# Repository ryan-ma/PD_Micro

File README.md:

# PD_Micro
ATMega32U4 Arduino board with USB-C PD Power Delivery and PPS

## Specs:
- ATmega32U4 running at 5 V and 16 MHz
- FUSB302 USB-C PHY (USB PD communication on CC pins)
- TPS62175 DC-DC for 5-20V input, 5V 500mA max output
- On-board 30V 10.4A P-channel MOSFET load switch
- 5 LEDs for power delivery voltage level
- 3 LEDs for power delivery current level
- 3.5 mm, 2 position terminal block for power output
- 1.6 x 0.7 inches (0.3 inches longer than pro micro)

# Basic Usage

Open `PD_Micro.ino` with Arduino Sketch. Choose board `Arduino Leoardo`

## Set power option
Allocate a PD_UFP object
```
class PD_UFP_c PD_UFP;
```

Initialize it with one of the power options. That sets the maximum voltage/current. 
```
PD_UFP.init(PD_POWER_OPTION_MAX_20V);
```

```
enum PD_power_option_t {
    PD_POWER_OPTION_MAX_5V      = 0,
    PD_POWER_OPTION_MAX_9V      = 1,
    PD_POWER_OPTION_MAX_12V     = 2,
    PD_POWER_OPTION_MAX_15V     = 3,
    PD_POWER_OPTION_MAX_20V     = 4,
    PD_POWER_OPTION_MAX_VOLTAGE = 5,
    PD_POWER_OPTION_MAX_CURRENT = 6,
    PD_POWER_OPTION_MAX_POWER   = 7,
};
```

## Run USB PD state machine
Before USB PD negotiation had completed, `PD_UFP.run()` must be called in a short interval, less than 10ms, to ensure state machine response to negotiation message in time. Long response time may result in a power reset cycle initiated by USB PD hosts.

## Wait for USB PD negotiation completed
`PD_UFP.is_power_ready()` is set when
- PD negotiation completed, PD host sent a power ready message, or
- PD host not exist, CC pins voltage is checked and the power level determined.

The negotiation process typically takes less than a second.

## Examine the negotiated power value
Examine the negotiated power value. Turn on the load switch only when the power requirements are met. PD Micro itself does not have PD over current protection. Any excessive power usage may trigger USB PD host power protection, result in voltage dip and MCU reset. 

```
PD_UFP.run();
if (PD_UFP.get_voltage() == PD_V(20.0) && PD_UFP.get_current() >= PD_A(1.5)) {
  PD_UFP.set_output(1);   // Turn on load switch 
  PD_UFP.set_led(1);      // Output reach 20V and 1.5A, set indicators on
} else {
  PD_UFP.set_output(0);   // Turn off load switch
  PD_UFP.blink_led(400);  // Output less than 20V or 1.5A, blink LED
}
```
For Fix power option, `PD_UFP.get_voltage()` in 50 mV units and `PD_UFP.get_current()` in 10mA units. Use marco `PD_V` and `PD_A` to simplify conversion.

## Changing power option in run time
Power options can be changed any time after PD negotiation.
```
PD_UFP.set_power_option(PD_POWER_OPTION_MAX_20V);
```

`PD_UFP.is_ps_transition()` is set during power transition, clear when new power is ready. 
Power transition takes a maximum time of 550ms according to PD specifications. Depends on the power adapter, it is usually shorter.

# USB PD 3.0 PPS (Programmable Power Supply)
USB PD3.0 introduces a new PPS (Programmable Power Supply) mode. If PD source supports PPS, It allows devices to negotiate precise voltage range from 3.3V to 5.9/11/16/21 V with 20 mV step. PPS also supports a coarse current limit, with the value in 50 mA step.

The library provides another set of procedures to request PPS. If source PPS is not available or not qualified, it will fall back to use the regular PD power option.

## Set voltage and current on startup
Instead of using `PD_UFP.init()`, use `PD_UFP.init_PPS()` to setup PPS voltage in 20 mV units and PPS current in 50 mA units. Use marco `PPS_V()` and `PPS_A()` to simplify conversion.
```
PD_UFP.init_PPS(PPS_V(4.2), PPS_A(2.0));
```
The default fall-back PD power option is 5V. It can be changed by an extra parameter.
```
PD_UFP.init_PPS(PPS_V(4.2), PPS_A(2.0), PD_POWER_OPTION_MAX_9V);
```

PD Micro use ATMega32U4 with safe operation 8MHz @ <4.5V. To request PPS below 4.5V, use `clock_prescale_set(clock_div_2)` to slow down the working frequency, and use `PD_UFP.clock_prescale_set(2)` to prescale the library internal clock.
```
PD_UFP.clock_prescale_set(2);
clock_prescale_set(clock_div_2);
```

## Wait for USB PD PPS trigger completed
Once PD negotiation is completed,
- If PPS is available and qualified, `PD_UFP.is_PPS_ready()` is set. 
- If PPS is not available or qualified, `PD_UFP.is_power_ready()` is set.

If PPS is successfully triggered, the output voltage and current will be the exact value provided in the startup. It is not required to examine negotiated voltage and current.
```
PD_UFP.run();
if (PD_UFP.is_PPS_ready()) {          // PPS trigger success
  PD_UFP.set_output(1);               // Turn on load switch 
  PD_UFP.set_led(1);                  // PPS output 4.2V 2.0A ready
} else if (PD_UFP.is_power_ready()) { // Fail to trigger PPS, fall back
  PD_UFP.set_output(0);               // Turn off load switch
  PD_UFP.blink_led(400);              // blink LED
}
```
For PPS, `PD_UFP.get_voltage()` in 20 mV units and `PD_UFP.get_current()` in 50 mA units. Use marco `PPS_V()` and `PPS_A()` to simplify conversion.

## Changing PPS voltage and current in run time
PPS settings can be changed any time after PPS ready. Similar to `PD_UFP.init_PPS()`, set voltage in 20 mV units and current in 50 mA units. Use Marco `PPS_V()` and `PPS_A()` to simplify conversion.
```
PD_UFP.set_PPS(PPS_V(3.3), PPS_A(2.0));
```

`PD_UFP.is_ps_transition()` is set during power transition, clear when new power is ready. 
Power transition takes a maximum time of 550 ms according to specification. It is usually less than 50ms in PPS mode. 

By calling `PD_UFP.set_PPS()`, the library re-evaluates all PPS source capabilities to find the best fit. If it fails to find one, it returns false, no power request, and power transition will happen.

To exit PPS mode, call `PD_UFP.set_power_option()` to clear PPS setting and fall back to regular power option mode.

# LED Indicators
There are 5 LEDs for voltage and 3 LEDs for current on PD_Micro, multiplexed by 6 internal IO pins. These are managed by the PD_UFP library. 

The library turn on voltage LED according to the following table

| Voltage Range | LED | 
| --- | --- |
| >= 3.3V && < 9V | 5V | 
| >= 9V && < 12V | 9V | 
| >= 12V && < 15V | 12V | 
| >= 15V && < 20V | 15V | 
| >= 20 | 20V | 

# Debugging
The library can log library status, source capabilities, protocol packets, with timestamps in the millisecond step to the serial port.

To use it, allocate PD_UFP object with derived class `PD_UFP_log_c`
```
class PD_UFP_log_c PD_UFP;
```
initialize hardware serial1 in setup.
```
void setup() {
  Serial1.begin(115200);
  ...
```
call `PD_UFP.print_status(Serial1)` inside `loop()`.
```
void loop() {
  PD_UFP.run();
  PD_UFP.print_status(Serial1);
  ...
```
Connect Pin 1 (PD3 / UART TX) and GND to external USB to UART to read serial messages.

PD Micro can be converted to serial passthrough mode and use it as USB to UART. I included these Arduino sketch examples in <a href="/examples">examples</a> folder.

## Debug raw packets
The library provides two log levels. Initialize PD_UFP with extra parameter `PD_LOG_LEVEL_VERBOSE` to output raw packets
```
class PD_UFP_log_c PD_UFP(PD_LOG_LEVEL_VERBOSE);
```
```
enum pd_log_level_t {
    PD_LOG_LEVEL_INFO,
    PD_LOG_LEVEL_VERBOSE
};
```

# Bootloader
PD Micro uses `Caterina-promicro16.hex` bootloader provided by Sparkfun. Program it by `avrdude` and set the corresponding `efuse`.
```
avrdude -p m32u4 -P usb -c avrispmkii -U flash:w:Caterina-promicro16.hex -U efuse:w:0xcb:m -U hfuse:w:0xd8:m -U lfuse:w:0xff:m
```

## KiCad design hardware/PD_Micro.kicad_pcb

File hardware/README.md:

# Schematic diagram
https://github.com/ryan-ma/PD_Micro/blob/master/hardware/PD_Micro_schematic-2020-06-01.pdf

# Interactive BOM
https://htmlpreview.github.io/?https://github.com/ryan-ma/PD_Micro/blob/master/hardware/PD_Micro_ibom-2020-06-01.html

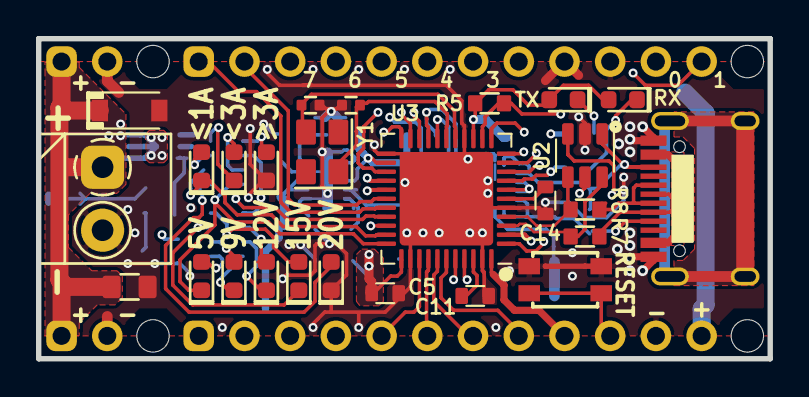
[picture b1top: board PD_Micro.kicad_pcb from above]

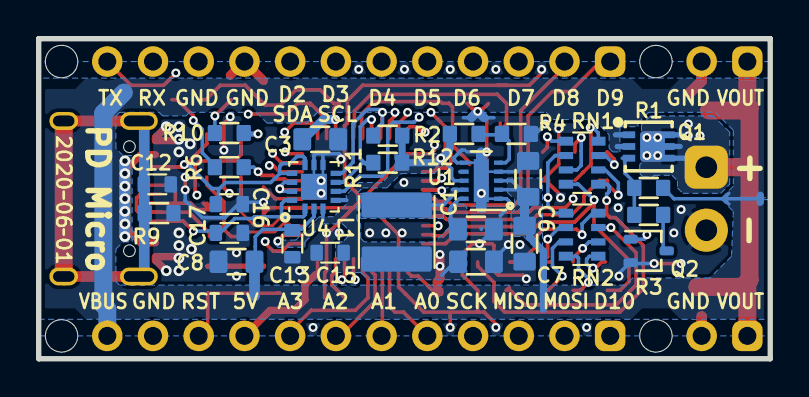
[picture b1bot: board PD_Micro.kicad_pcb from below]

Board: 4 copper layers, 40.6 x 17.8 mm, 61 parts (31 on the bottom side), 56 nets.

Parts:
C1, C2, C3: 10uF; C_0805
C4, C6, C7, C8: 1uF 50V; C_0805
C5, C11, C13, C15: 0.1uF; C_0603
C9, C10: 22pF; C_0402
C12: 10nF; C_0603
C14: 1uF; C_0603
C16, C17: 330pF; C_0603
D1: SMF22A; D_SOD-123
D2, D3, D4, D5, D6, D7, D8, D9, D10, D11: LED; LED_0603_1608Metric
H1, H2, H3, H4: MountingHole; D1_8_PAD
J1, J2: Conn_01x02; PinHeader_1x02_P2.54mm_Vertical
J3: Conn_01x02; TerminalBlock_3.5mm_2P
J4, J5: Conn_01x12; PinHeader_1x12_P2.54mm_Vertical
L1: 10uH; L_4012
Q1: DMP3017SFK; DFN-2523-6
Q2: DTC143E; SOT-323_SC-70
R1, R5, R9: 10k; R_0603
R2: 270k; R_0603
R3: 1k; R_0603
R4: 51k; R_0603
R6, R10: 33k; R_0603
R7, R8: 22R; R_0603
R11, R12: 2k; R_0603
RN1, RN2: 4x33k; R_Array_Convex_4x0603
SW1: SW_Push; SW_SPST_3.5x3mm
U1: TPS62175DQC; WSON-10-1EP_2x3mm_P0.5mm_EP0.84x2.4mm
U2: SRV05-4; SOT-23-6
U3: ATmega32U4-MU; QFN-44-1EP_7x7mm_P0.5mm_EP5.2x5.2mm
U4: FUSB302BMPX; WQFN-14-1EP_2.5x2.5mm_P0.5mm_EP1.45x1.45mm
USB1: HRO-TYPE-C-31-M-12
Y1: 16MHz; Crystal_SMD_3225-4Pin_3.2x2.5mm

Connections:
+5V: C1.1, C2.1, C3.1, C5.1, C15.1, D5.2, D11.2, J5.9, L1.2, R2.1, R5.1, R11.1, R12.1, RN1.2, RN2.1, U1.8, U1.10, U2.5, U3.2, U3.7, U3.14, U3.24, U3.34, U3.44, U4.3, U4.4, U4.12, U4.13
/CC1: C17.2, U2.3, U4.1, U4.14, USB1.4
/CC2: C16.2, U2.1, U4.10, U4.11, USB1.10
/DN: R7.2, USB1.5, USB1.7
/DP: R8.2, USB1.6, USB1.8
/OUT: C4.1, D1.1, J1.1, J2.1, J3.1, Q1.4, Q1.5, Q1.6
/SHIELD: C12.1, R9.1, USB1.13
/SW1: L1.1, U1.9
A0: J5.5, U3.36
A1: J5.6, U3.37
A2: J5.7, U3.38
A3: J5.8, U3.39
D2: J4.8, R11.2, U3.19, U4.7
D3: J4.7, R12.2, U3.18, U4.6
D4: J4.6, U3.25
D5: J4.5, U3.31
D6: J4.4, U3.27
D7: J4.3, U3.1, U4.5
D8: J4.2, U3.28
D9: J4.1, U3.29
D10: J5.1, Q2.1, U3.30
GND: C1.2, C2.2, C3.2, C4.2, C5.2, C6.2, C7.2, C8.2, C9.2, C10.2, C11.2, C12.2, C13.2, C14.2, C15.2, C16.1, C17.1, D1.2, D2.1, D6.1, J1.2, J2.2, J3.2, J4.9, J4.10, J5.11, Q2.2, R4.2, R9.2, SW1.1, U1.1, U1.4, U1.6, U1.11, U2.2, U3.5, U3.15, U3.23, U3.35, U3.43, U3.45, U4.8, U4.9, U4.15, USB1.1, USB1.12
MISO: J5.3, U3.11
MOSI: J5.2, U3.10
unnamed: C9.1, U3.17, Y1.1
unnamed: C10.1, U3.16, Y1.3
unnamed: C11.1, U3.42
unnamed: C14.1, U3.6
unnamed: D2.2, RN1.1
unnamed: D3.2, RN1.7
unnamed: D4.2, RN1.3
unnamed: D5.1, R6.1
unnamed: D6.2, RN1.5
unnamed: D7.2, RN2.8
unnamed: D8.2, RN2.2
unnamed: D9.2, RN2.6
unnamed: D10.2, RN2.5
unnamed: D11.1, R10.1
unnamed: Q1.3, R1.2, R3.1
unnamed: Q2.3, R3.2
unnamed: R2.2, R4.1, U1.5
unnamed: R6.2, U3.8
unnamed: R7.1, U2.6, U3.3
unnamed: R8.1, U2.4, U3.4
unnamed: R10.2, U3.22
PB7: D7.1, RN2.7, U3.12
PC7: D3.1, RN1.6, U3.32
PD6: D4.1, RN1.8, U3.26
PE2: D10.1, RN1.4, U3.33
PF0: D8.1, RN2.3, U3.41
PF1: D9.1, RN2.4, U3.40
RESET: J5.10, R5.2, SW1.2, U3.13
RXI: J4.11, U3.20
SCK: J5.4, U3.9
TXO: J4.12, U3.21
VBUS: C6.1, C7.1, C8.1, C13.1, J5.12, Q1.1, Q1.2, R1.1, U1.2, U1.3, U4.2, USB1.2, USB1.11

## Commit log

2020-03-10 Initial Add
2020-11-18 Update to latest version
2020-12-16 Add hardware readme
2021-01-04 Add gitignore and gitattributes
2021-01-04 Move ardunio sketch files to sub folder
2021-01-04 Add USB PD 3.0 PPS support
2021-01-04 Add example templates
2021-01-13 Optimize RAM usage and log status message
2021-01-25 Code refactoring. Add raw packet logging
2021-01-25 Add Kicad design files
2021-01-28 Bug fix and add example
2021-06-16 Fix PPS current parsing. Add power type string in logging
2021-08-24 Fix power negotiation fail if number of PDO is more than 6
